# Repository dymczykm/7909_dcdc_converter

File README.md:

# Alpine 7909 DC/DC converter
An improved DC/DC converter design for Alpine 7909.

Uses a Traco 6W converter to get symmetric +/-12V and then ultralow noise, ultrahigh PSRR linear regulators (LT3045, LT3094) to regulate the voltages down to +/-10V.

The board is smaller than the original and fits nicely into the space available.

**Warning** The PCBs have not been tested as of now, use at your own risk.

## 3D view

## Component list

Most components specific to this are contained in the [CSV file](digikey_bom.csv). Please note that it does not contain components I had already at hand, so double check it against the schematic.

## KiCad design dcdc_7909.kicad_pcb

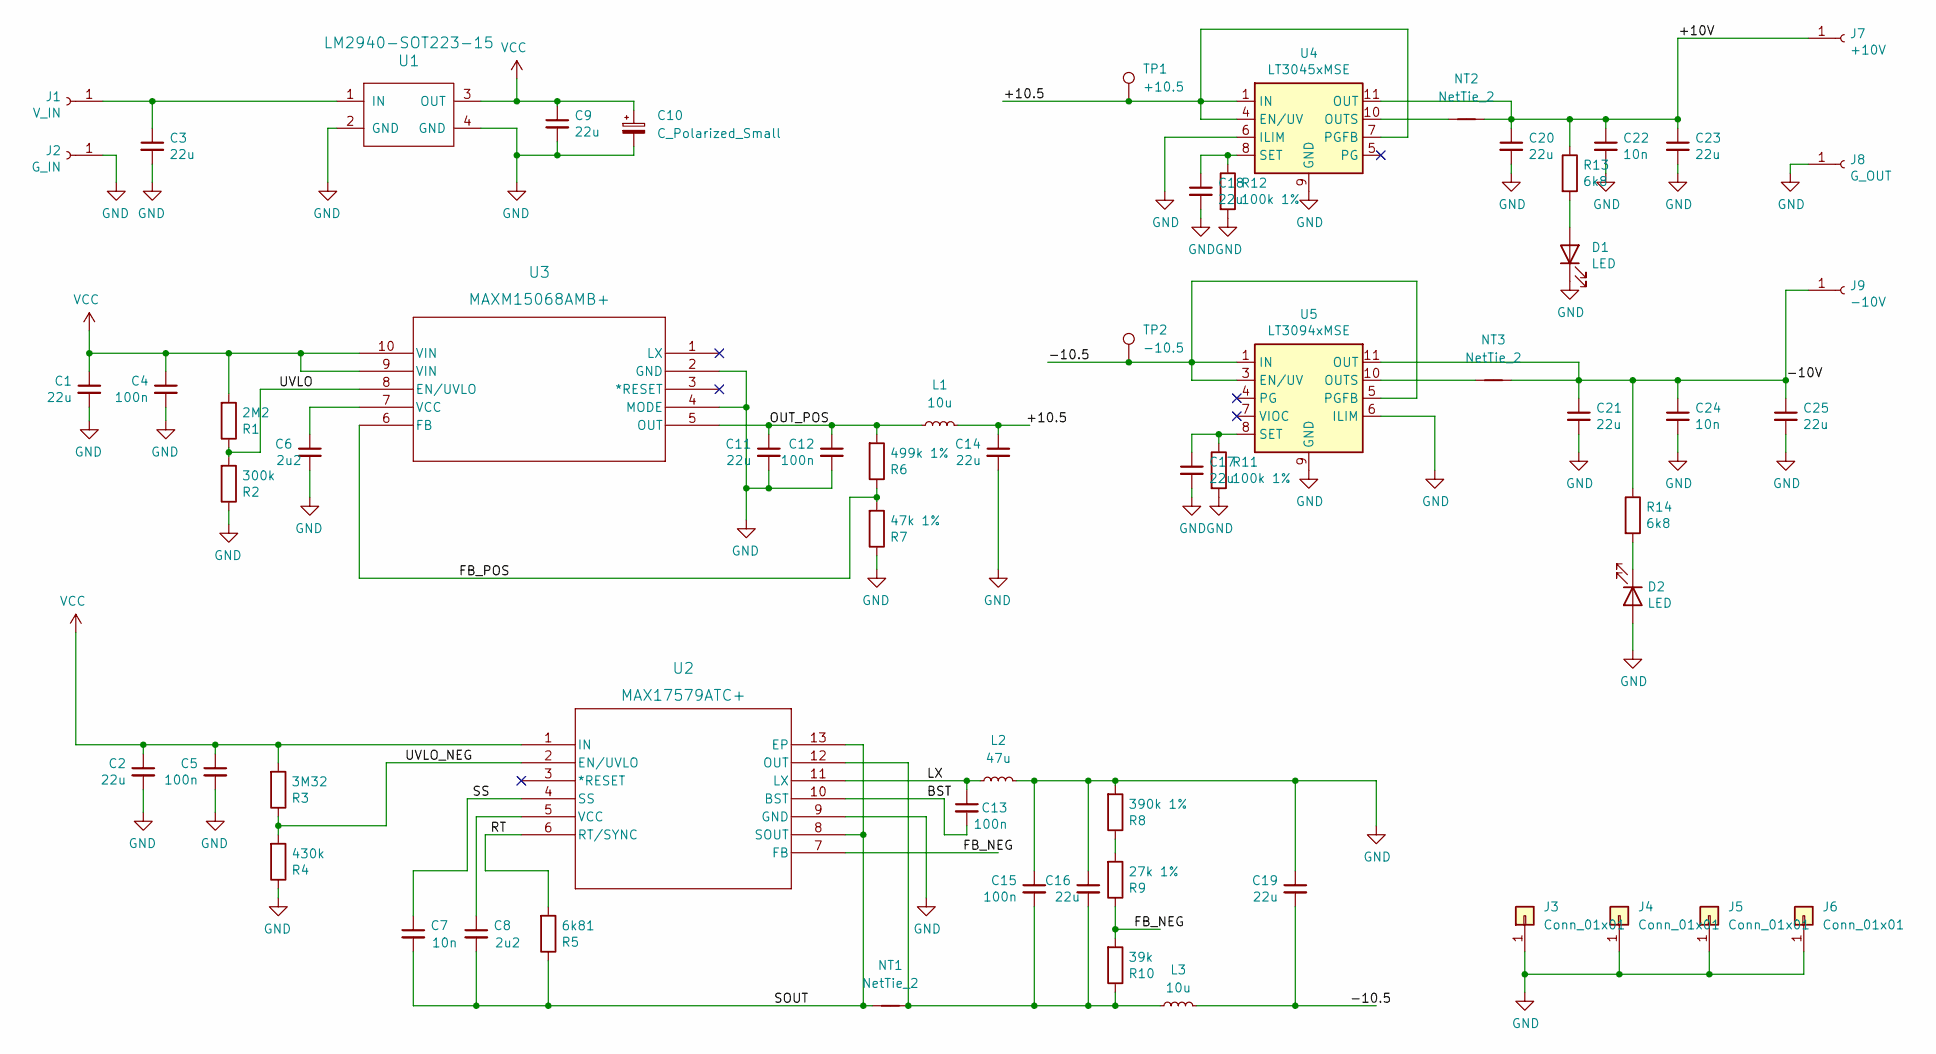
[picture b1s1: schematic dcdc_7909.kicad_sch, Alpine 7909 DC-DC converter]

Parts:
C1, C2, C3, C9, C11, C14, C16, C19, C20, C21, C23, C25: 22u; C_1210_3225Metric; LCSC C426653
C4, C5, C12, C13, C15: 100n; C_0402_1005Metric; LCSC C307331
C6, C8: 2u2; C_1206_3216Metric; LCSC C50254
C7, C22, C24: 10n; C_0402_1005Metric; LCSC C15195
C10: C_Polarized_Small; CP_Elec_6.3x5.9
C17, C18: 22u; C_1206_3216Metric; LCSC C12891
D1, D2: LED; LED_0805_2012Metric_Pad1.15x1.40mm_HandSolder; LCSC DO NOT POPULATE
J1: V_IN; SolderWire-0.75sqmm_1x01_D1.25mm_OD3.5mm; LCSC DO NOT POPULATE
J2: G_IN; SolderWire-0.75sqmm_1x01_D1.25mm_OD3.5mm; LCSC DO NOT POPULATE
J3, J4, J5, J6: Conn_01x01; SolderWirePad_1x01_SMD_1x2mm; LCSC DO NOT POPULATE
J7: +10V; SolderWire-0.75sqmm_1x01_D1.25mm_OD3.5mm; LCSC DO NOT POPULATE
J8: G_OUT; SolderWire-0.75sqmm_1x01_D1.25mm_OD3.5mm; LCSC DO NOT POPULATE
J9: -10V; SolderWire-0.75sqmm_1x01_D1.25mm_OD3.5mm; LCSC DO NOT POPULATE
L1, L3: 10u; L_0805_2012Metric; LCSC DO NOT POPULATE
L2: 47u; Wurth 74408063680; LCSC DO NOT POPULATE
NT1, NT2, NT3: NetTie_2; NetTie-2_SMD_Pad0.5mm; LCSC DO NOT POPULATE
R1: 2M2; R_0402_1005Metric; LCSC C11490
R2: 300k; R_0402_1005Metric; LCSC C334752
R3: 3M32; R_0402_1005Metric; LCSC C477691
R4: 430k; R_0402_1005Metric; LCSC C25786
R5: 6k81; R_0402_1005Metric; LCSC C284661
R6: 499k 1%; R_0402_1005Metric; LCSC C407728
R7: 47k 1%; R_0402_1005Metric; LCSC C25792
R8: 390k 1%; R_0402_1005Metric; LCSC C52036
R9: 27k 1%; R_0402_1005Metric; LCSC C52036
R10: 39k; R_0402_1005Metric; LCSC C284379
R11, R12: 100k 1%; R_0603_1608Metric; LCSC C25803
R13, R14: 6k8; R_0402_1005Metric; LCSC C25917
TP1: +10.5; TestPoint_THTPad_D1.0mm_Drill0.5mm; LCSC DO NOT POPULATE
TP2: -10.5; TestPoint_THTPad_D1.0mm_Drill0.5mm; LCSC DO NOT POPULATE
U1: LM2940-SOT223-15; SOT-223; LCSC C81094
U2: MAX17579ATC+; 21-0664_TD1233&plus_1C_MXM; LCSC C5691155
U3: MAXM15068AMB+; 10-eMGA (3x2.6); LCSC DO NOT POPULATE
U4: LT3045xMSE; MSOP-12-1EP_3x4mm_P0.65mm_EP1.65x2.85mm; LCSC C666577
U5: LT3094xMSE; MSOP-12-1EP_3x4mm_P0.65mm_EP1.65x2.85mm; LCSC C498217

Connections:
/+10.5: C14.1, L1.1, TP1.1, U4.1 (IN), U4.2 (IN), U4.3 (IN), U4.4 (EN/UV), U4.7 (PGFB)
/+10V: C20.1, C22.1, C23.1, J7.1, NT2.2, R13.1, U4.11 (OUT), U4.12 (OUT)
/-10.5: C19.2, L3.1, TP2.1, U5.1 (IN), U5.2 (IN), U5.3 (EN/UV), U5.5 (PGFB), U5.13 (IN)
/-10V: C21.1, C24.1, C25.1, J9.1, NT3.2, R14.1, U5.11 (OUT), U5.12 (OUT)
/BST: C13.2, U2.10 (BST)
/FB_NEG: R9.1, R10.2, U2.7 (FB)
/FB_POS: R6.1, R7.2, U3.6 (FB)
/LX: C13.1, L2.1, U2.11 (LX)
/OUT_POS: C11.1, C12.1, L1.2, R6.2, U3.5 (OUT)
/RT: R5.2, U2.6 (RT/SYNC)
/SOUT: C7.2, C8.2, NT1.1, R5.1, U2.8 (SOUT), U2.13 (EP)
/SS: C7.1, U2.4 (SS)
/UVLO: R1.1, R2.2, U3.8 (EN/UVLO)
/UVLO_NEG: R3.1, R4.2, U2.2 (EN/UVLO)
GND: C1.2, C2.2, C3.2, C4.2, C5.2, C6.2, C9.2, C10.2, C11.2, C12.2, C14.2, C15.1, C16.1, C17.2, C18.2, C19.1, C20.2, C21.2, C22.2, C23.2, C24.2, C25.2, D1.1 (K), D2.2 (A), J2.1, J3.1, J4.1, J5.1, J6.1, J8.1, L2.2, R2.1, R4.1, R7.1, R8.2, R11.2, R12.2, U1.2 (GND), U1.4 (GND), U2.9 (GND), U3.2 (GND), U3.4 (MODE), U4.6 (ILIM), U4.9 (GND), U4.13 (GND), U5.6 (ILIM), U5.9 (GND)
unnamed: C3.1, J1.1, U1.1 (IN)
unnamed: C6.1, U3.7 (VCC)
unnamed: C8.1, U2.5 (VCC)
unnamed: C15.2, C16.2, L3.2, NT1.2, R10.1, U2.12 (OUT)
unnamed: C17.1, R11.1, U5.8 (SET)
unnamed: C18.1, R12.1, U4.8 (SET)
unnamed: D1.2 (A), R13.2
unnamed: D2.1 (K), R14.2
unnamed: NT2.1, U4.10 (OUTS)
unnamed: NT3.1, U5.10 (OUTS)
unnamed: R8.1, R9.2
VCC: C1.1, C2.1, C4.1, C5.1, C9.1, C10.1, R1.2, R3.2, U1.3 (OUT), U2.1 (IN), U3.9 (VIN), U3.10 (VIN)

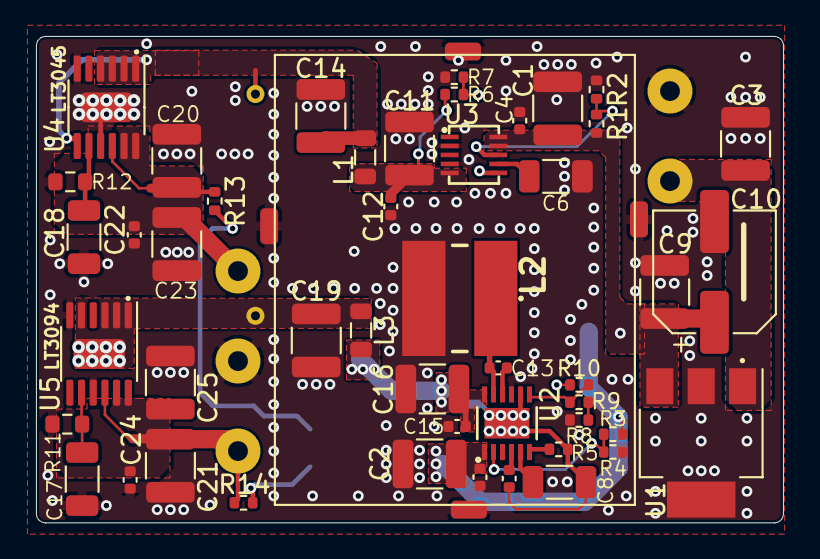
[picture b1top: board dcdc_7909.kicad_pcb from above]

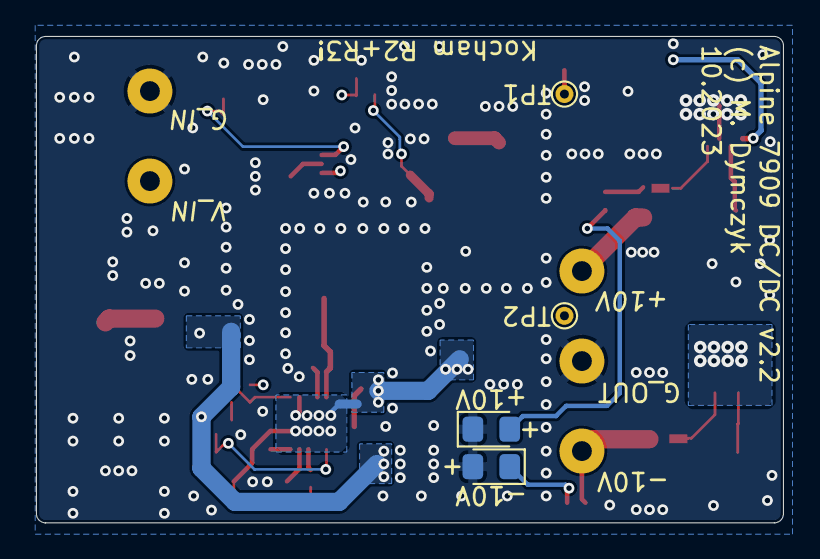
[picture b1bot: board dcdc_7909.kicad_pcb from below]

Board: 4 copper layers, 41.5 x 27.0 mm, 63 parts (5 on the bottom side), 27 nets.

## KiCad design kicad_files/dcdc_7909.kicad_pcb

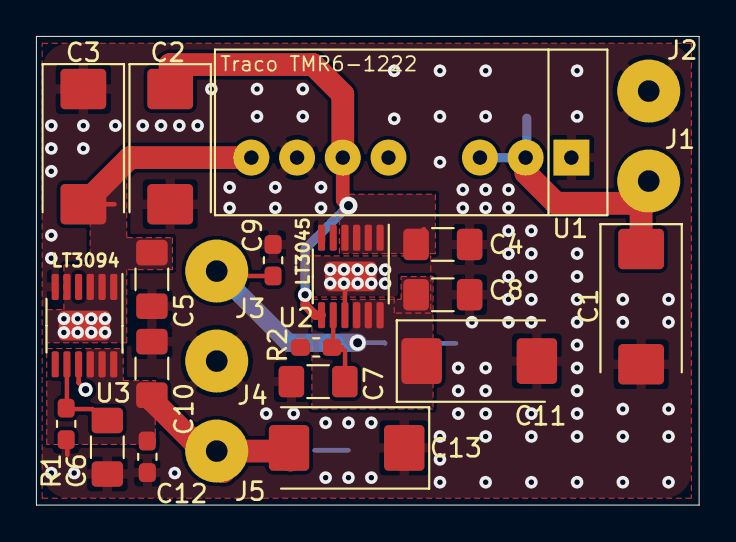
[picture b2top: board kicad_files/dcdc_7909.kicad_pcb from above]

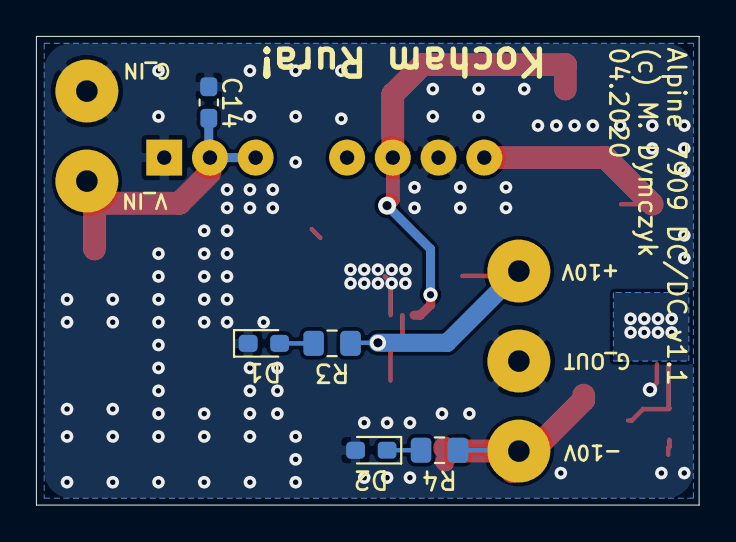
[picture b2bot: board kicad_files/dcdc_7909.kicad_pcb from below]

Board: 2 copper layers, 36.8 x 26.0 mm, 28 parts (5 on the bottom side), 10 nets.

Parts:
C1: 100u 25v; CP_EIA-7343-31_Kemet-D_Pad2.25x2.55mm_HandSolder
C2, C3, C11, C13: 100u 16V; CP_EIA-7343-31_Kemet-D_Pad2.25x2.55mm_HandSolder
C4, C5, C6, C7, C8, C10: 10u X7R; C_1206_3216Metric_Pad1.42x1.75mm_HandSolder
C9, C12, C14: 10n; C_0603_1608Metric_Pad1.05x0.95mm_HandSolder
D1, D2: LED; LED_0603_1608Metric_Pad1.05x0.95mm_HandSolder
J1: V_IN; SolderWirePad_1x01_Drill1.2mm
J2: G_IN; SolderWirePad_1x01_Drill1.2mm
J3: +10V; SolderWirePad_1x01_Drill1.2mm
J4: G_OUT; SolderWirePad_1x01_Drill1.2mm
J5: -10V; SolderWirePad_1x01_Drill1.2mm
R1, R2: 100k; R_0603_1608Metric_Pad1.05x0.95mm_HandSolder
R3, R4: 820; R_0805_2012Metric_Pad1.15x1.40mm_HandSolder
U1: TMR6; Traco_TMR6
U2: LT3045xMSE; MSOP-12-1EP_3x4mm_P0.65mm_EP1.65x2.85mm
U3: LT3094xMSE; MSOP-12-1EP_3x4mm_P0.65mm_EP1.65x2.85mm

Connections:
+12V: C8.1, C9.1, C11.1, J3.1, R3.1, U2.10, U2.11, U2.12
-12V: C10.1, C12.1, C13.2, J5.1, R4.1, U3.10, U3.11, U3.12
GND: C1.2, C2.2, C3.1, C4.2, C5.2, C6.2, C7.2, C8.2, C9.2, C10.2, C11.2, C12.2, C13.1, C14.2, D1.1, D2.2, J2.1, J4.1, R1.2, R2.2, U1.1, U1.7, U2.6, U2.9, U2.13, U3.6, U3.9
unnamed: C2.1, C4.1, U1.6, U2.1, U2.2, U2.3, U2.4, U2.7
unnamed: C3.2, C5.1, U1.8, U3.1, U3.2, U3.3, U3.5, U3.13
unnamed: C6.1, R1.1, U3.8
unnamed: C7.1, R2.1, U2.8
unnamed: D1.2, R3.2
unnamed: D2.1, R4.2
VCC: C1.1, C14.1, J1.1, U1.2, U1.3

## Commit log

2020-04-25 design v1.0
2020-04-26 v1.1
2020-04-26 v1.1 finished, gerber files added
2020-12-28 Update the files.
2020-12-28 Update the LICENSE
2023-06-28 working on v2.
2023-06-30 V2 PCB almost finished.
2023-07-02 One more iteration over the PCB to fit the filtering in the can.
2023-07-03 Updated ground fill zones.
2023-07-03 Updated BOM.
2023-07-04 Corrected the ground plane.
2023-07-05 New version ready for JLCPCB.
2023-08-01 Files send for production.
2023-08-10 WIP on version 2.1, routing mostly done.
2023-08-11 Rev 2.1 finished.
2023-08-11 Final v2.1.
2023-08-13 Initial commit of the production files, not final yet!
2023-08-13 V2.1 ready for JLCPCB.
2023-09-15 ltspice simulation.
2023-09-21 Reworking the board with MAX76x/
2023-09-21 Reworking almost completed.
2023-09-23 Ready design, but MAX764 cannot be used because of the Vin-Vout differential.
2023-09-26 Switched to MAX77x + Si9435.
2023-10-06 Last version before switching to Maxim modules.
2023-10-06 Added MAXM15068.
2023-10-06 New version based on MAXM15068 and MAX17579.
2023-10-06 Calculated the resistor values.
2023-10-06 Filled out LCSC components refs.
2023-10-06 Minor.
2023-10-18 Fixed the 2u2 cap footprints.
2023-10-18 Sent for production.
2023-11-15 Doing calcs + removing caps that might introduce noise.
2023-11-15 Before restructuring max17579.
2023-11-17 Fix footprints of MAX and MAXM.
